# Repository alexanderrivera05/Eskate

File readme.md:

# ESKATE
Building an electric skateboard from scratch. This repository contains all the necessary files organized into sub-directories to see the various aspects of the project. This project includes a 3d printed remote with custom PCB using a STM32 uC, 3d printed battery enclosure with custom BMS solution, and ESC using another STM32 uC with 3d Printed enclosure.

## Directories
1. Remote
2. Battery
3. ESC

# Updates
This is an ongoing project as of 2020 and will be updated with regular progress.

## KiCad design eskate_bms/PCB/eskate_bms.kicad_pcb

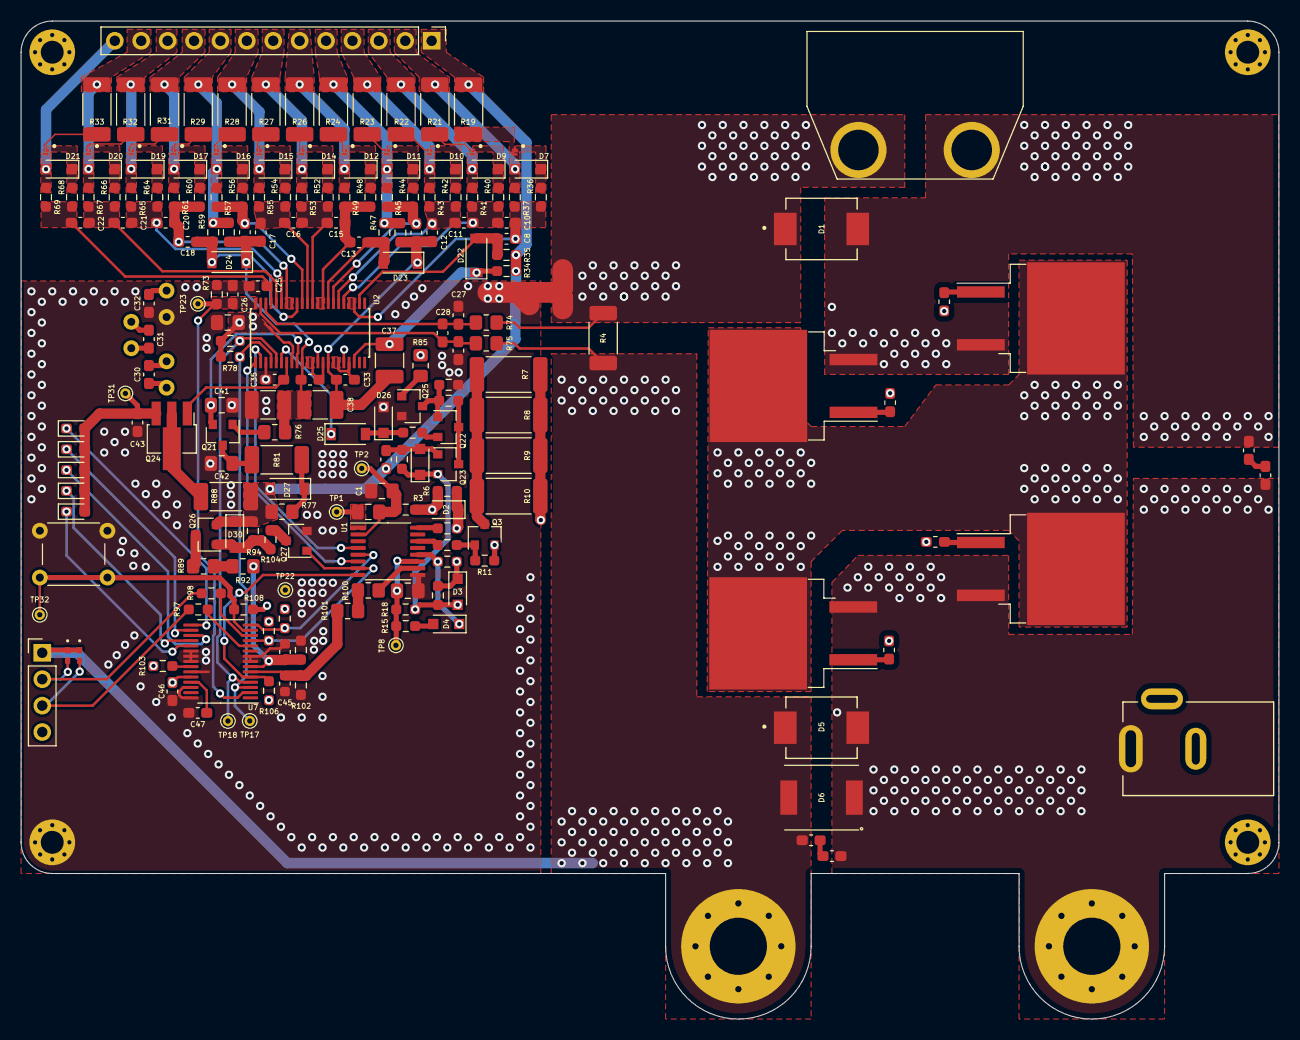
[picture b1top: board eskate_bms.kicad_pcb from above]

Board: 4 copper layers, 121.0 x 96.0 mm, 220 parts (0 on the bottom side), 129 nets.

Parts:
C1, C5: 0.01u; C_0805_2012Metric_Pad1.18x1.45mm_HandSolder
C2: 1.5u; C_0805_2012Metric_Pad1.18x1.45mm_HandSolder
C3, C4, C6, C7, C27, C28, C29, C46, C47: 0.1u; C_0603_1608Metric_Pad1.08x0.95mm_HandSolder
C8, C10, C11, C12, C13, C15, C16, C17, C18, C20, C21, C22, C23, C24, C25, C43: 0.22u; C_0603_1608Metric_Pad1.08x0.95mm_HandSolder
C26, C36: 470p; C_0603_1608Metric_Pad1.08x0.95mm_HandSolder
C30, C31, C32: 4700p; C_0603_1608Metric_Pad1.08x0.95mm_HandSolder
C33, C34, C35: 1u; C_0603_1608Metric_Pad1.08x0.95mm_HandSolder
C37, C38, C39: 10u; C_1210_3225Metric_Pad1.33x2.70mm_HandSolder
C40: 4.7u; C_0805_2012Metric_Pad1.18x1.45mm_HandSolder
C41, C42: 1u; C_0805_2012Metric_Pad1.18x1.45mm_HandSolder
C44, C45: 3300p; C_0603_1608Metric
D1, D5: 60V; DIOM7959X262N
D2, D3: 16V; D_SOD-323_HandSoldering
D4, D28, D30: 18V; D_SOD-323_HandSoldering
D6: 200V; ES3D-E3_57T
D7, D9, D10, D11, D12, D14, D15, D16, D17, D19, D20, D21: 5.6V; D_SOD-323_HandSoldering
D22, D23, D24, D25, D27: 100V; D_SOD-123
D26: 3.9V; D_SOD-323_HandSoldering
D31, D32, D33, D34, D35: SMD_GREEN; D_0603_1608Metric_Pad1.05x0.95mm_HandSolder
FB1, FB2, FB3, FB4: 220; L_0603_1608Metric_Pad1.05x0.95mm_HandSolder
G1: LOGO; alexembedded_logo_10mm
H1, H2: MountingHole_Pad; MountingHole_5.5mm_Pad_Via
H3, H4, H5, H6: MountingHole_Pad; MountingHole_2.2mm_M2_Pad_Via
J1: Conn_01x02_Male; XT90PW
J3: Barrel_Jack_Switch; SWITCHCRAFT_RAPC722X
J5: Conn_01x13_Male; PinHeader_1x13_P2.54mm_Vertical
J8: Conn_01x04_Male; PinHeader_1x04_P2.54mm_Vertical
NT1: Net-Tie_2; NetTie-2_SMD_Pad2.0mm
NT2, NT3: Net-Tie_2; NetTie-2_SMD_Pad0.25mm
Q1, Q2, Q4, Q5: 100V; TO-263-2
Q3, Q23, Q26: -100V; SOT-23
Q6, Q8, Q9, Q10, Q11, Q13, Q14, Q15, Q16, Q18, Q19, Q20: CSD13381F4; TRANS_CSD13380F3
Q21, Q22, Q25, Q27: 100V; SOT-23
Q24: 100V; SOT-89-3_Handsoldering
R3, R15, R18, R97, R98: 100; R_0603_1608Metric_Pad0.98x0.95mm_HandSolder
R4: 0.001; R_2010_5025Metric_Pad1.40x2.65mm_HandSolder
R6, R11, R16, R79, R84: 10M; R_0603_1608Metric_Pad0.98x0.95mm_HandSolder
R7, R8, R9, R10: 1.2k; R_2512_6332Metric_Pad1.40x3.35mm_HandSolder
R12, R13, R14: 620; R_0603_1608Metric_Pad0.98x0.95mm_HandSolder
R19, R21, R22, R23, R24, R26, R27, R28, R29, R31, R32, R33: 28.7; R_2010_5025Metric_Pad1.40x2.65mm_HandSolder
R34, R35, R37, R41, R43, R45, R46, R47, R49, R53, R55, R57, R58, R59, R61, R65, R67, R69: 1k; R_0603_1608Metric_Pad0.98x0.95mm_HandSolder
R36, R40, R42, R44, R48, R52, R54, R56, R60, R64, R66, R68, R78, R82, R99, R102: 10k; R_0603_1608Metric_Pad0.98x0.95mm_HandSolder
R73: 499k; R_0603_1608Metric_Pad0.98x0.95mm_HandSolder
R74, R75: 100; R_0805_2012Metric_Pad1.20x1.40mm_HandSolder
R76, R77, R85: 100k; R_0805_2012Metric_Pad1.20x1.40mm_HandSolder
R80: 51k; R_0603_1608Metric_Pad0.98x0.95mm_HandSolder
R81: 1k; R_2010_5025Metric_Pad1.40x2.65mm_HandSolder
R87: 1M; R_0603_1608Metric_Pad0.98x0.95mm_HandSolder
R88: 750; R_2010_5025Metric_Pad1.40x2.65mm_HandSolder
R89, R92, R100, R101: 300k; R_0805_2012Metric_Pad1.20x1.40mm_HandSolder
R94, R103: 100k; R_0603_1608Metric_Pad0.98x0.95mm_HandSolder
R104, R108: 220k; R_0603_1608Metric_Pad0.98x0.95mm_HandSolder
R105, R106: 510k; R_0603_1608Metric_Pad0.98x0.95mm_HandSolder
R107: 113k; R_0603_1608Metric_Pad0.98x0.95mm_HandSolder
SW1: SW_MEC_5E; SW_MEC_NO
TH1, TH2, TH3: 10k; 103AT-2
TP1, TP2, TP8, TP17, TP18, TP22, TP23, TP31, TP32: TestPoint; TestPoint_THTPad_D1.0mm_Drill0.5mm
U1: BQ76200PW; TSSOP-16_4.4x5mm_P0.65mm
U2: BQ76940; TSSOP-44_4.4x11.2mm_P0.5mm
U3, U4: TPD1E10B06DPYT; DIO_TPD1E05U06DPYR
U7: BQ78350; TSSOP-30_4.4x7.8mm_P0.5mm

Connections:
+BATT: C3.2, D1.2, D2.2, J1.1, Q1.3, Q2.3, R3.1, R6.1, R7.2, R8.2, R9.2, R10.2
-BATT: D1.1, J1.2, NT1.1, NT2.1, R4.2
/BQ76200/CD: Q1.2, Q2.2, Q3.2, Q4.2, Q5.2, R11.2
/BQ76200/CGATE: D2.1, FB1.2, FB2.2, R6.2, R12.2
/BQ76200/CHG: R12.1, U1.16
/BQ76200/CHG_EN: U1.4, U2.2
/BQ76200/CP_EN: R105.2, U1.5, U7.15
/BQ76200/DGATE: D3.1, FB3.2, FB4.2, R14.2, R16.1
/BQ76200/DSG: D4.1, R14.1, U1.12
/BQ76200/DSG_EN: U1.6, U2.1
/BQ76200/PACKDIV: R100.1, U1.10
/BQ76200/PCHG: R13.1, U1.14
/BQ76200/PCHG_EN: R106.2, U1.8, U7.5
/BQ76200/PGATE: Q3.1, R11.1, R13.2
/BQ76200/PMON_EN: Q27.1, R107.2, U1.7, U7.12
/BQ76200/SNSN: NT3.2, R75.2
/BQ76200/SNSP: NT2.2, R74.2
/BQ76940/ALERT: C26.2, R73.1, TP23.1, U2.44, U7.2
/BQ76940/C0: D21.2, J5.13, Q20.3, R69.2
/BQ76940/C1: D20.2, J5.12, Q19.3, R33.2, R67.2
/BQ76940/C1/vc+: C21.2, C22.1, R66.1, R67.1, U2.40
/BQ76940/C1/vc-: C22.2, C25.2, R68.1, R69.1, U2.41
/BQ76940/C2: D19.2, J5.11, Q18.3, R32.2, R65.2
/BQ76940/C2/vc+: C20.2, C21.1, R64.1, R65.1, U2.39
/BQ76940/C3: D17.2, J5.10, Q16.3, R31.2, R61.2
/BQ76940/C3/vc+: C18.2, C20.1, R60.1, R61.1, U2.37, U2.38
/BQ76940/C4: D16.2, J5.9, Q15.3, R29.2, R57.2, R58.2, R59.2
/BQ76940/C4/vc+: C18.1, D24.2, R59.1, U2.36
/BQ76940/C5: D15.2, J5.8, Q14.3, R28.2, R55.2
/BQ76940/C5/vc+: C16.2, C17.1, R54.1, R55.1, U2.34
/BQ76940/C5/vcb: C24.1, R56.1, R57.1, U2.35
/BQ76940/C6: D14.2, J5.7, Q13.3, R27.2, R53.2
/BQ76940/C6/vc+: C15.2, C16.1, R52.1, R53.1, U2.33
/BQ76940/C7: D12.2, J5.6, Q11.3, R26.2, R49.2
/BQ76940/C7/vc+: C13.2, C15.1, R48.1, R49.1, U2.31, U2.32
/BQ76940/C8: D11.2, J5.5, Q10.3, R24.2, R45.2, R46.2, R47.2
/BQ76940/C8/vc+: C13.1, D23.2, R47.1, U2.30
/BQ76940/C9: D10.2, J5.4, Q9.3, R23.2, R43.2
/BQ76940/C9/vc+: C11.2, C12.1, R42.1, R43.1, U2.28
/BQ76940/C9/vcb: C23.1, R44.1, R45.1, U2.29
/BQ76940/C10: D9.2, J5.3, Q8.3, R22.2, R41.2
/BQ76940/C10/vc+: C10.2, C11.1, R40.1, R41.1, U2.27
/BQ76940/C11: D7.2, J5.2, Q6.3, R21.2, R37.2
/BQ76940/C11/vc+: C8.2, C10.1, R36.1, R37.1, U2.25, U2.26
/BQ76940/C12/vc+: C8.1, D22.2, R35.1, U2.24
/BQ76940/LEDP: C43.2, D31.2, D32.2, D33.2, D34.2, D35.2, Q24.3, TP31.1
/BQ76940/SCL: R82.2, TP18.1, U2.5, U7.4
/BQ76940/SDA: R78.2, TP17.1, U2.4, U7.3
BAT: C1.2, C2.1, R3.2, TP2.1, U1.2
C15: C36.2, D27.2, D30.1, J5.1, Q26.2, R19.2, R34.2, R35.2, R77.1, R88.1, R94.1
CAP1: C35.2, Q24.1, U2.7
GND: C1.1, C5.1, C25.1, C26.1, C27.2, C29.1, C32.1, C35.1, C39.1, C40.1, C41.1, C42.1, C43.1, C44.2, C45.2, C46.2, C47.2, D26.2, H3.1, NT1.2, Q25.2, Q27.2, R73.2, R84.2, R99.2, R102.2, SW1.3, SW1.4, TH3.2, U1.9, U2.3, U7.8, U7.9, U7.21, U7.22, U7.23, U7.25, U7.28, U7.30
unnamed: C3.1, C4.2
unnamed: C6.1, C7.2
unnamed: C27.1, C28.1, R74.1, U2.42
unnamed: C28.2, C29.2, R75.1, U2.43
unnamed: C33.1, U2.16, U2.17, U2.19
unnamed: C34.1, U2.11, U2.12, U2.14
unnamed: C36.1, D28.2, Q23.1, R79.2
unnamed: C42.2, Q21.3, R81.2
unnamed: C44.1, R92.1, R99.1, U7.7
unnamed: C45.1, R101.2, R102.1, U7.6
unnamed: C47.1, U7.27
unnamed: D4.2, R15.2
unnamed: D7.1, Q6.1, R36.2
unnamed: D9.1, Q8.1, R40.2
unnamed: D10.1, Q9.1, R42.2
unnamed: D11.1, Q10.1, R44.2
unnamed: D12.1, Q11.1, R48.2
unnamed: D14.1, Q13.1, R52.2
unnamed: D15.1, Q14.1, R54.2
unnamed: D16.1, Q15.1, R56.2
unnamed: D17.1, Q16.1, R60.2
unnamed: D19.1, Q18.1, R64.2
unnamed: D20.1, Q19.1, R66.2
unnamed: D21.1, Q20.1, R68.2
unnamed: D25.2, D26.1, R80.2
unnamed: D27.1, R77.2, R81.1
unnamed: D30.2, Q26.1, R94.2, R104.2
unnamed: D31.1, U7.16
unnamed: D32.1, U7.17
unnamed: D33.1, U7.18
unnamed: D34.1, U7.19
unnamed: D35.1, U7.20
unnamed: FB1.1, Q1.1
unnamed: FB2.1, Q2.1
unnamed: FB3.1, Q4.1
unnamed: FB4.1, Q5.1
unnamed: Q3.3, R7.1, R8.1, R9.1, R10.1
unnamed: Q6.2, R19.1
unnamed: Q8.2, R21.1
unnamed: Q9.2, R22.1
unnamed: Q10.2, R23.1
unnamed: Q11.2, R24.1
unnamed: Q13.2, R26.1
unnamed: Q14.2, R27.1
unnamed: Q15.2, R28.1
unnamed: Q16.2, R29.1
unnamed: Q18.2, R31.1
unnamed: Q19.2, R32.1
unnamed: Q20.2, R33.1
unnamed: Q21.1, R76.1
unnamed: Q22.1, Q25.3, R84.1, R87.2
unnamed: Q22.2, R80.1
unnamed: Q22.3, Q23.3, R87.1
unnamed: Q24.2, R88.2
unnamed: Q25.1, R85.1
unnamed: Q26.3, R89.1
unnamed: Q27.3, R104.1
unnamed: R89.2, R92.2
unnamed: R97.2, U7.11
unnamed: R98.2, U7.13
unnamed: R100.2, R101.1
unnamed: R103.2, U7.24
unnamed: R108.2, SW1.1, SW1.2, TP32.1, U7.14
PACK: C5.2, R15.1, R18.2, TP8.1, U1.11
PACK+: C4.1, C7.1, D3.2, D5.2, D6.1, D28.1, H1.1, J3.1, Q4.3, Q5.3, Q23.2, R16.2, R18.1, R79.1
PACK-: C6.2, D5.1, D6.2, H2.1, J3.2, J8.1, NT3.1, R4.1, U3.1, U4.1
REGOUT: C40.2, C46.1, R78.1, R82.1, R85.2, R103.1, R105.1, R106.1, R107.1, R108.1, TP22.1, U2.8, U7.26
REGSRC: C41.2, Q21.2, U2.9
SMBC: J8.2, R98.1, U3.2
SMBD: J8.3, R97.1, U4.2
TS1: C32.2, D25.1, TH3.1, U2.6
TS2: C31.2, TH2.1, U2.13
TS3: C30.2, TH1.1, U2.18
VC5X: C17.2, C24.2, C31.1, C34.2, C38.1, C39.2, D24.1, R58.1, R76.2, TH2.2, U2.10
VC10X: C12.2, C23.2, C30.1, C33.2, C37.1, C38.2, D23.1, R46.1, TH1.2, U2.15
VC15X: C37.2, D22.1, R34.1, U2.20
VDDCP: C2.2, TP1.1, U1.1

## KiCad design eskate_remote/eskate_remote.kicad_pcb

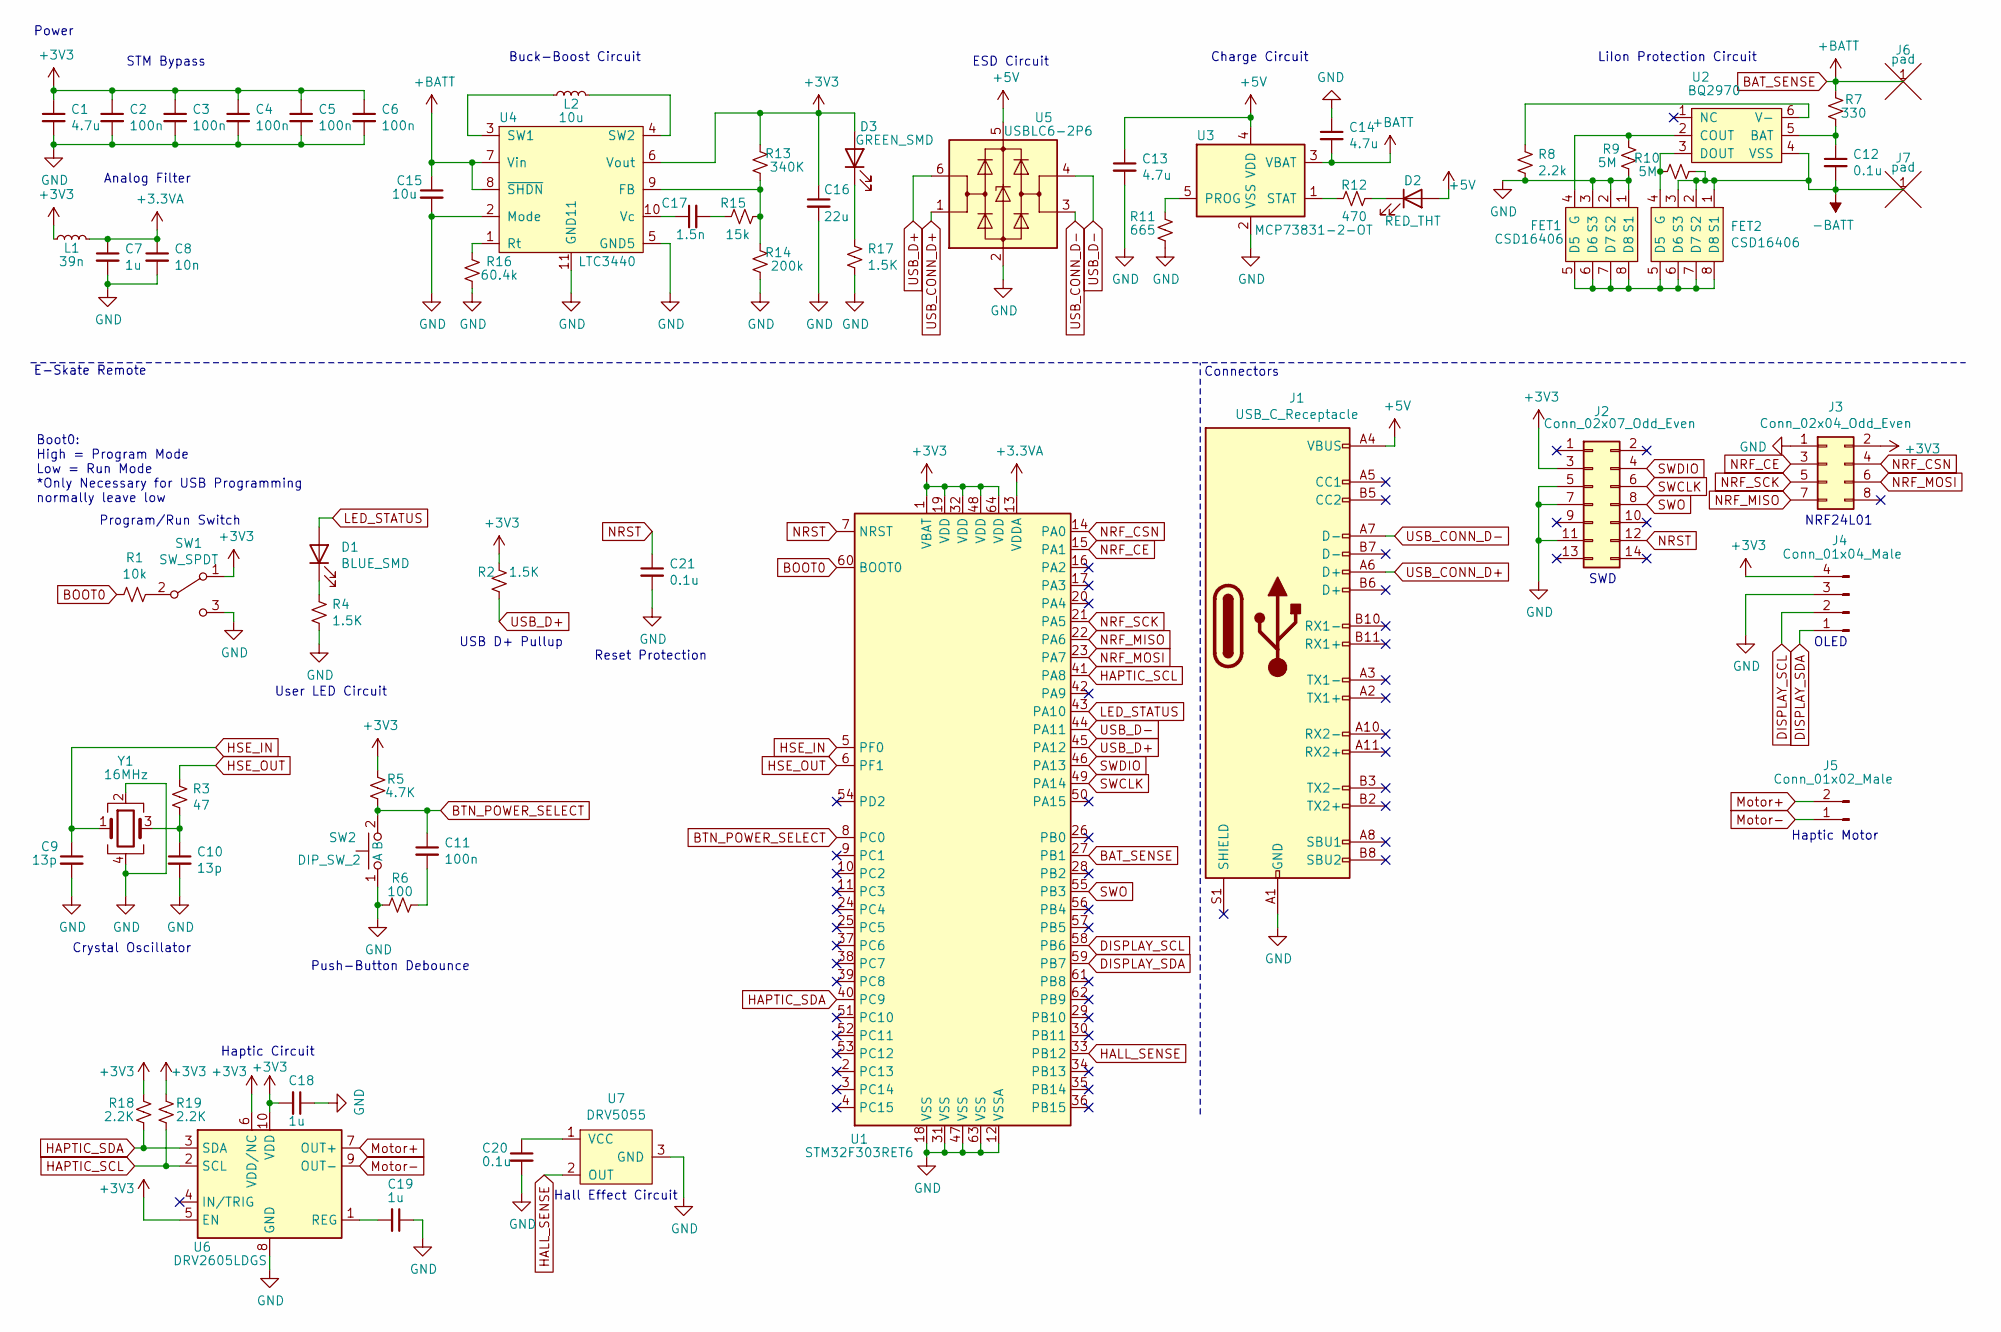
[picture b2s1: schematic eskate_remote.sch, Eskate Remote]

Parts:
C1: 4.7u; C_0402_1005Metric_Pad0.74x0.62mm_HandSolder
C2, C3, C4, C5, C6, C11: 100n; C_0402_1005Metric_Pad0.74x0.62mm_HandSolder
C7, C18, C19: 1u; C_0402_1005Metric_Pad0.74x0.62mm_HandSolder
C8: 10n; C_0402_1005Metric_Pad0.74x0.62mm_HandSolder
C9, C10: 13p; C_0402_1005Metric_Pad0.74x0.62mm_HandSolder
C12, C20, C21: 0.1u; C_0402_1005Metric_Pad0.74x0.62mm_HandSolder
C13, C14: 4.7u; C_0805_2012Metric_Pad1.18x1.45mm_HandSolder
C15: 10u; C_0805_2012Metric_Pad1.18x1.45mm_HandSolder
C16: 22u; C_1210_3225Metric_Pad1.33x2.70mm_HandSolder
C17: 1.5n; C_0402_1005Metric_Pad0.74x0.62mm_HandSolder
D1: BLUE_SMD; LED_0603_1608Metric_Pad1.05x0.95mm_HandSolder
D2: RED_THT; LED_D5.0mm
D3: GREEN_SMD; LED_0603_1608Metric_Pad1.05x0.95mm_HandSolder
FET1, FET2: CSD16406
J1: USB_C_Receptacle; MOLEX_105450-0101
J2: Conn_02x07_Odd_Even; M50-3610742R
J3: Conn_02x04_Odd_Even; PinHeader_2x04_P2.54mm_Vertical
J4: Conn_01x04_Male; PinHeader_1x04_P2.54mm_Vertical
J5: Conn_01x02_Male; PinHeader_1x02_P2.54mm_Vertical
J6, J7: pad; LiIon_Pad
L1: 39n; L_0603_1608Metric_Pad1.05x0.95mm_HandSolder
L2: 10u; CDRH6D38NP
R1: 10k; R_0402_1005Metric_Pad0.72x0.64mm_HandSolder
R2, R4, R17: 1.5K; R_0402_1005Metric_Pad0.72x0.64mm_HandSolder
R3: 47; R_0402_1005Metric_Pad0.72x0.64mm_HandSolder
R5: 4.7K; R_0402_1005Metric_Pad0.72x0.64mm_HandSolder
R6: 100; R_0402_1005Metric_Pad0.72x0.64mm_HandSolder
R7: 330; R_0603_1608Metric_Pad0.98x0.95mm_HandSolder
R8: 2.2k; R_0603_1608Metric_Pad0.98x0.95mm_HandSolder
R9, R10: 5M; R_1206_3216Metric_Pad1.30x1.75mm_HandSolder
R11: 665; R_0603_1608Metric_Pad0.98x0.95mm_HandSolder
R12: 470; R_0603_1608Metric_Pad0.98x0.95mm_HandSolder
R13: 340K; R_0805_2012Metric_Pad1.20x1.40mm_HandSolder
R14: 200k; R_0603_1608Metric_Pad0.98x0.95mm_HandSolder
R15: 15k; R_0603_1608Metric_Pad0.98x0.95mm_HandSolder
R16: 60.4k; R_0603_1608Metric_Pad0.98x0.95mm_HandSolder
R18, R19: 2.2K; R_0603_1608Metric_Pad0.98x0.95mm_HandSolder
SW1: SW_SPDT; JS102011SAQN
SW2: DIP_SW_2; DIP_Switch_2
U1: STM32F303RET6; LQFP-64_10x10mm_P0.5mm
U2: BQ2970
U3: MCP73831-2-OT; MCP73831
U4: LTC3440
U5: USBLC6-2P6; SOT-23-6_Handsoldering
U6: DRV2605LDGS; VSSOP-10_3x3mm_P0.5mm
U7: DRV5055
Y1: 16MHz; ABM11W-16MHZ

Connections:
+3.3VA: C7.1, C8.1, L1.2, U1.13 (VDDA)
+3V3: C1.1, C2.1, C3.1, C4.1, C5.1, C6.1, C16.1, C18.2, D3.2 (A), J2.3, J3.2, J4.4, L1.1, R2.2, R5.1, R13.1, R18.2, R19.2, SW1.1 (A), U1.1 (VBAT), U1.19 (VDD), U1.32 (VDD), U1.48 (VDD), U1.64 (VDD), U4.6 (Vout), U6.5 (EN), U6.6 (VDD/NC), U6.10 (VDD)
+5V: C13.1, D2.2 (A), J1.A4 (VBUS), J1.A9 (VBUS), J1.B4 (VBUS), J1.B9 (VBUS), U3.4 (VDD), U5.5 (VBUS)
-BATT: C12.2, FET2.1 (S1), FET2.2 (S2), FET2.3 (S3), J7.1, R10.2, U2.4 (VSS)
BAT_SENSE: C14.2, C15.1, J6.1, R7.1, U1.27 (PB1), U3.3 (VBAT), U4.7 (Vin), U4.8 (~SHDN)
BOOT0: R1.2, U1.60 (BOOT0)
BTN_POWER_SELECT: C11.1, R5.2, SW2.2 (B), U1.8 (PC0)
DISPLAY_SCL: J4.2, U1.58 (PB6)
DISPLAY_SDA: J4.1, U1.59 (PB7)
GND: C1.2, C2.2, C3.2, C4.2, C5.2, C6.2, C7.2, C8.2, C9.2, C10.2, C13.2, C14.1, C15.2, C16.2, C18.1, C19.1, C20.2, C21.2, FET1.1 (S1), FET1.2 (S2), FET1.3 (S3), J1.A1 (GND), J1.A12 (GND), J1.B1 (GND), J1.B12 (GND), J2.5, J2.7, J2.11, J3.1, J4.3, R4.1, R6.1, R8.1, R9.1, R11.2, R14.2, R16.2, R17.1, SW1.3 (C), SW2.1 (A), U1.12 (VSSA), U1.18 (VSS), U1.31 (VSS), U1.47 (VSS), U1.63 (VSS), U3.2 (VSS), U4.2 (Mode), U4.5 (GND5), U4.11 (GND11), U5.2 (GND), U6.8 (GND), U7.3 (GND), Y1.2, Y1.4
HALL_SENSE: U1.33 (PB12), U7.2 (OUT)
HAPTIC_SCL: R19.1, U1.41 (PA8), U6.2 (SCL)
HAPTIC_SDA: R18.1, U1.40 (PC9), U6.3 (SDA)
HSE_IN: C9.1, U1.5 (PF0), Y1.1
HSE_OUT: R3.2, U1.6 (PF1)
LED_STATUS: D1.2 (A), U1.43 (PA10)
Motor+: J5.2, U6.7 (OUT+)
Motor-: J5.1, U6.9 (OUT-)
NRF_CE: J3.3, U1.15 (PA1)
NRF_CSN: J3.4, U1.14 (PA0)
NRF_MISO: J3.7, U1.22 (PA6)
NRF_MOSI: J3.6, U1.23 (PA7)
NRF_SCK: J3.5, U1.21 (PA5)
NRST: C21.1, J2.12, U1.7 (NRST)
unnamed: C10.1, R3.1, Y1.3
unnamed: C11.2, R6.2
unnamed: C12.1, R7.2, U2.5 (BAT)
unnamed: C17.1, U4.10 (Vc)
unnamed: C17.2, R15.1
unnamed: C19.2, U6.1 (REG)
unnamed: C20.1, U7.1 (VCC)
unnamed: D1.1 (K), R4.2
unnamed: D2.1 (K), R12.2
unnamed: D3.1 (K), R17.2
unnamed: FET1.4 (G), R9.2, U2.2 (COUT)
unnamed: FET1.5 (D5), FET1.6 (D6), FET1.7 (D7), FET1.8 (D8), FET2.5 (D5), FET2.6 (D6), FET2.7 (D7), FET2.8 (D8)
unnamed: FET2.4 (G), R10.1, U2.3 (DOUT)
unnamed: L2.1, U4.3 (SW1)
unnamed: L2.2, U4.4 (SW2)
unnamed: R1.1, SW1.2 (B)
unnamed: R8.2, U2.6 (V-)
unnamed: R11.1, U3.5 (PROG)
unnamed: R12.1, U3.1 (STAT)
unnamed: R13.2, R14.1, R15.2, U4.9 (FB)
unnamed: R16.1, U4.1 (Rt)
SWCLK: J2.6, U1.49 (PA14)
SWDIO: J2.4, U1.46 (PA13)
SWO: J2.8, U1.55 (PB3)
USB_CONN_D+: J1.A6 (D+), U5.1 (I/O1)
USB_CONN_D-: J1.A7 (D-), U5.3 (I/O2)
USB_D+: R2.1, U1.45 (PA12), U5.6 (I/O1)
USB_D-: U1.44 (PA11), U5.4 (I/O2)

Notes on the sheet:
Power
Connectors
E-Skate Remote
LiIon Protection Circuit
Charge Circuit
ESD Circuit
STM Bypass
Analog Filter
Buck-Boost Circuit
NRF24L01
SWD
OLED
Haptic Motor
Haptic Circuit
Hall Effect Circuit
Crystal Oscillator
Push-Button Debounce
USB D+ Pullup
Program/Run Switch
Boot0: High = Program Mode Low = Run Mode *Only Necessary for USB Programming normally leave low
User LED Circuit
Reset Protection

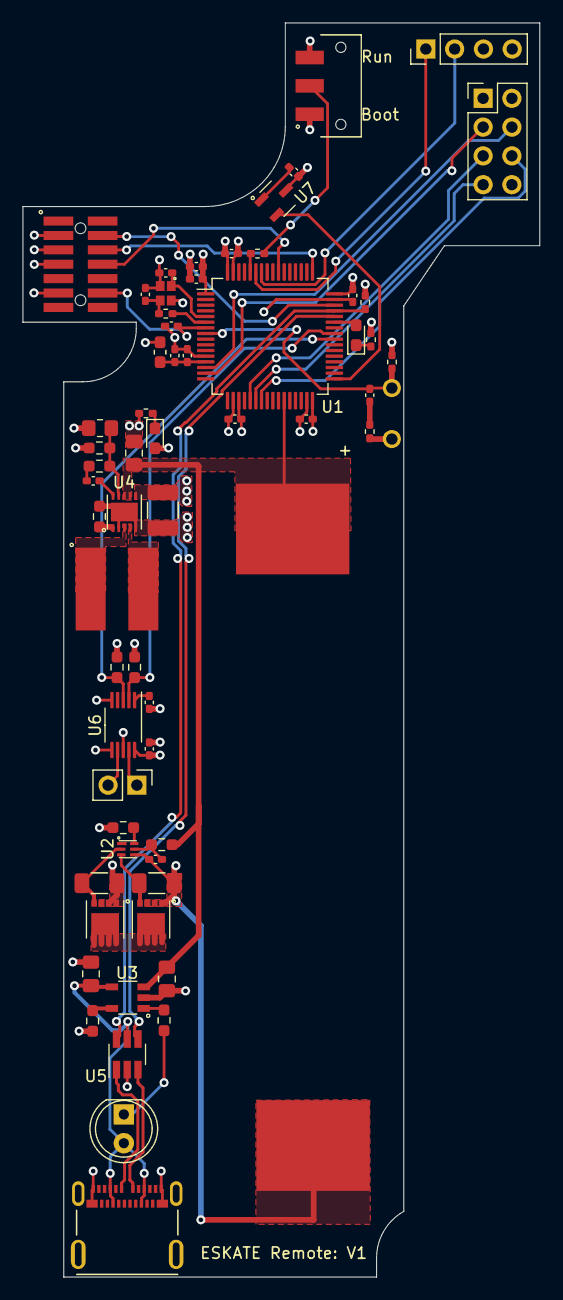
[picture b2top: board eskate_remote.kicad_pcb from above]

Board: 4 copper layers, 45.6 x 110.7 mm, 64 parts (0 on the bottom side), 52 nets.

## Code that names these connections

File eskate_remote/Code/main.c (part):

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
  ssd1306_Init();

  NRF24_begin(NRF_CE_GPIO_Port, NRF_CSN_Pin, NRF_CE_Pin, hspi1);
  NRF24_stopListening();
  NRF24_openWritingPipe(TxpipeAddrs);
  NRF24_setAutoAck(false);
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				DRV2605_setWaveform(17);
				DRV2605_go();
			}else if(buttonTim >= 10000){
				HAL_GPIO_TogglePin(LED_STATUS_GPIO_Port, LED_STATUS_Pin);
				DRV2605_setWaveform(64);
				DRV2605_go();
			}
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  __HAL_RCC_GPIOB_CLK_ENABLE();

  /*Configure GPIO pin Output Level */
  HAL_GPIO_WritePin(GPIOA, NRF_CSN_Pin|NRF_CE_Pin|LED_STATUS_Pin, GPIO_PIN_RESET);

  /*Configure GPIO pin : BTN_POWER_SELECT_Pin */
  GPIO_InitStruct.Pin = BTN_POWER_SELECT_Pin;
  GPIO_InitStruct.Mode = GPIO_MODE_IT_RISING_FALLING;
  GPIO_InitStruct.Pull = GPIO_NOPULL;
  HAL_GPIO_Init(BTN_POWER_SELECT_GPIO_Port, &GPIO_InitStruct);

  /*Configure GPIO pins : NRF_CSN_Pin NRF_CE_Pin LED_STATUS_Pin */
  GPIO_InitStruct.Pin = NRF_CSN_Pin|NRF_CE_Pin|LED_STATUS_Pin;
  GPIO_InitStruct.Mode = GPIO_MODE_OUTPUT_PP;
  GPIO_InitStruct.Pull = GPIO_NOPULL;
  GPIO_InitStruct.Speed = GPIO_SPEED_FREQ_LOW;
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void HAL_GPIO_EXTI_Callback(uint16_t GPIO_Pin)
{
  /* Prevent unused argument(s) compilation warning */
	if(HAL_GPIO_ReadPin(BTN_POWER_SELECT_GPIO_Port, BTN_POWER_SELECT_Pin)){
		HAL_TIM_Base_Stop_IT(&htim3);
		buttonFlag = 1;
	}else if(!HAL_GPIO_ReadPin(BTN_POWER_SELECT_GPIO_Port, BTN_POWER_SELECT_Pin)){
		HAL_TIM_Base_Start_IT(&htim3);
	}
}
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
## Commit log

2020-11-20 Initial readme commit
2020-11-26 uploaded V1 of PCB
2021-03-13 Added Folder System and Main.c
2021-03-27 Added BMS Rev1 *Not Working

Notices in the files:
eskate_remote/Code/main.c:
© Copyright (c) 2020 STMicroelectronics.
All rights reserved.
This software component is licensed by ST under BSD 3-Clause license,
the "License"; You may not use this file except in compliance with the
License. You may obtain a copy of the License at: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
(C) COPYRIGHT STMicroelectronics *****END OF FILE
